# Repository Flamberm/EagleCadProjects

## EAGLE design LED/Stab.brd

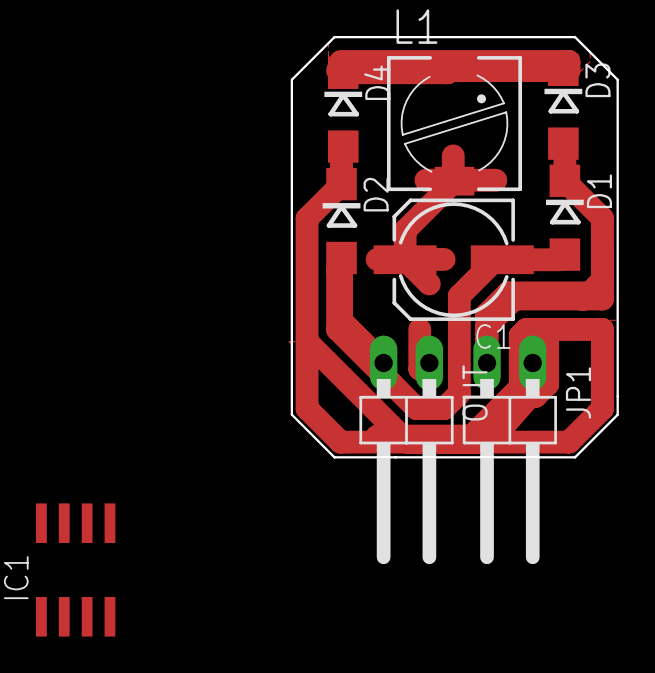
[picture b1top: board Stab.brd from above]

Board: 2 copper layers, 18.1 x 23.3 mm, 9 parts (0 on the bottom side), 5 nets.

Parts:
C1: 153CLV-0605
D1, D2, D3, D4: DO214AC
IC1: 78L12SMD; SO08
JP1: 1X02/90
L1: PIS2816
OUT: 1X02/90

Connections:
AC1: D1.C, D3.A, JP1.2
AC2: D2.C, D4.A, JP1.1
GND: C1.-, D1.A, D2.A, IC1.2, IC1.3, IC1.6, IC1.7, OUT.2
unnamed: D3.C, D4.C, L1.1
VCC: C1.+, L1.2

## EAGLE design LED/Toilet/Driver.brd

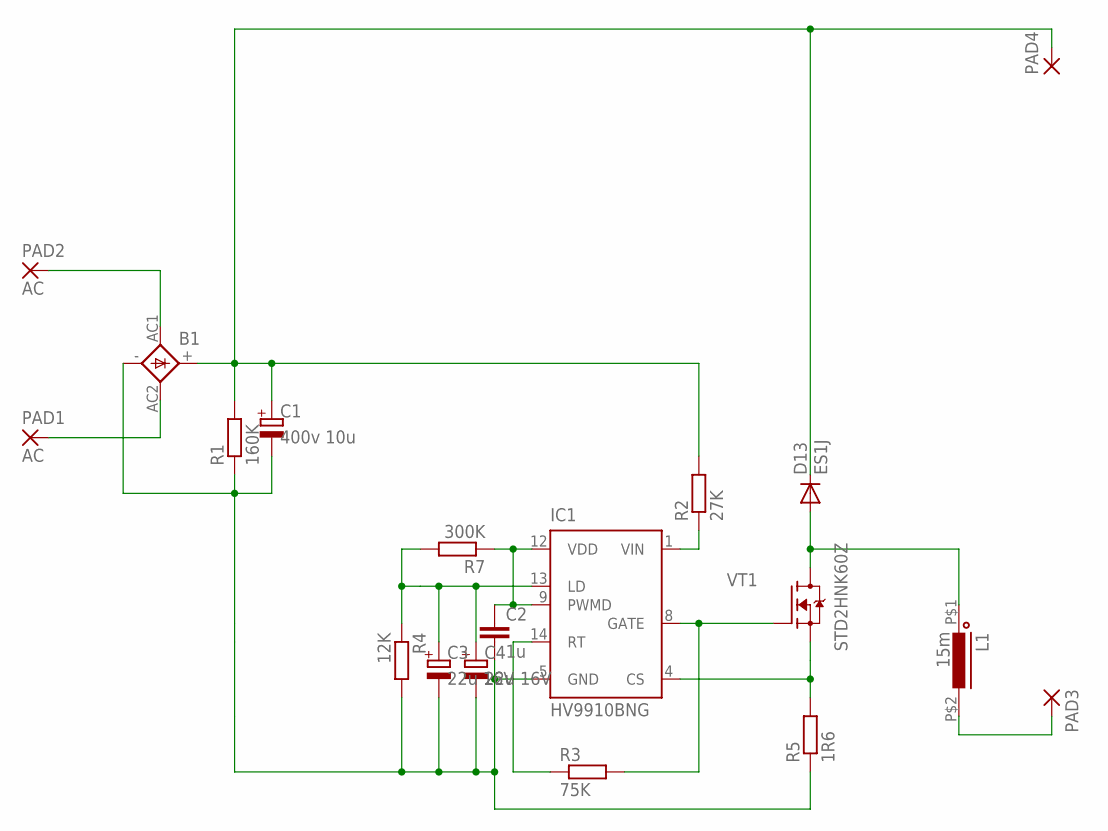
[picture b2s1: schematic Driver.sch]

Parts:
B1: BRIDGEMBS; MBS
C1: 400v 10u; E3,5-8
C2: 1u; C0805
C3, C4: 22u 16V; CT3528
D13: ES1J; DO214AC
IC1: HV9910BNG; SOIC-16NG
L1: 15m; SL1016
PAD1, PAD2: AC; SMD2,54-5,08
PAD3, PAD4: SMD5; SMD2,54-5,08
R1: 160K; MF-0125
R2: 27K; MF-2
R3: 75K; R0805
R4: 12K; R0805
R5: 1R6; MF-05
R7: 300K; R0805
VT1: STD2HNK60Z; DPAK

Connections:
unnamed: B1.AC1, PAD2.1
unnamed: B1.AC2, PAD1.1
unnamed: B1.-, C1.-, C2.2, C3.-, C4.-, IC1.5 (GND), R1.1, R4.2, R5.1
unnamed: C3.+, C4.+, IC1.13 (LD), R4.1, R7.2
unnamed: B1.+, C1.+, D13.C, PAD4.1, R1.2, R2.2
unnamed: IC1.1 (VIN), R2.1
unnamed: IC1.4 (CS), R5.2, VT1.S
unnamed: IC1.14 (RT), R3.1
unnamed: IC1.8 (GATE), R3.2, VT1.G
unnamed: L1.P$2 (2), PAD3.1
unnamed: D13.A, L1.P$1 (1), VT1.D
unnamed: C2.1, IC1.9 (PWMD), IC1.12 (VDD), R7.1

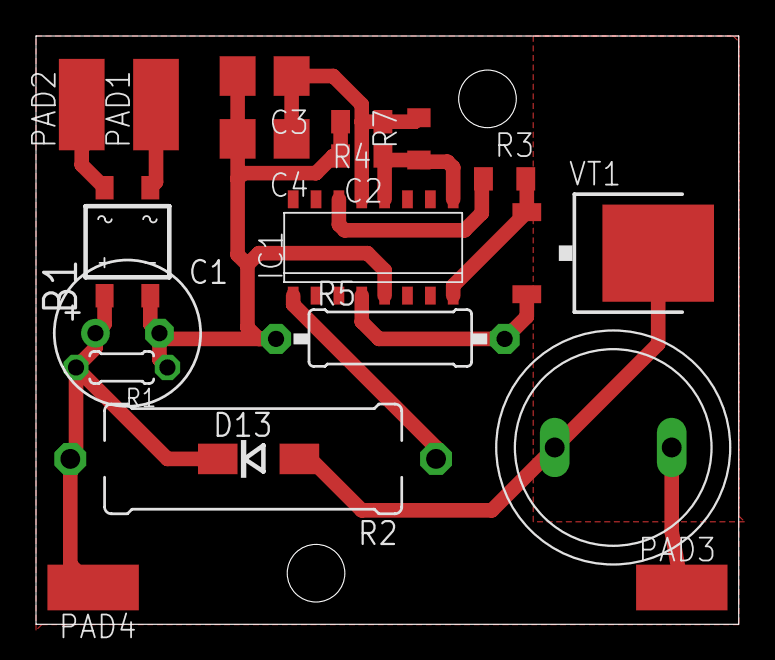
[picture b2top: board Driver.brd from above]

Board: 2 copper layers, 39.0 x 32.7 mm, 19 parts (0 on the bottom side), 12 nets.

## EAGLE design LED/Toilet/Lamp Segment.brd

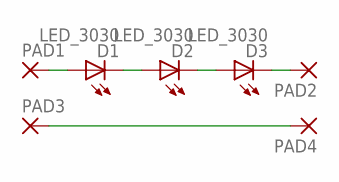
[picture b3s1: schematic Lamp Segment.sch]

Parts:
D1, D2, D3: LED_3030; LED3030
PAD1, PAD2, PAD3, PAD4: SMD5; SMD2,54-5,08

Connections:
1: D1.P$1 (A), PAD1.1
2: D1.P$2 (C), D2.P$1 (A)
3: D2.P$2 (C), D3.P$1 (A)
4: D3.P$2 (C), PAD2.1
BP: PAD3.1, PAD4.1

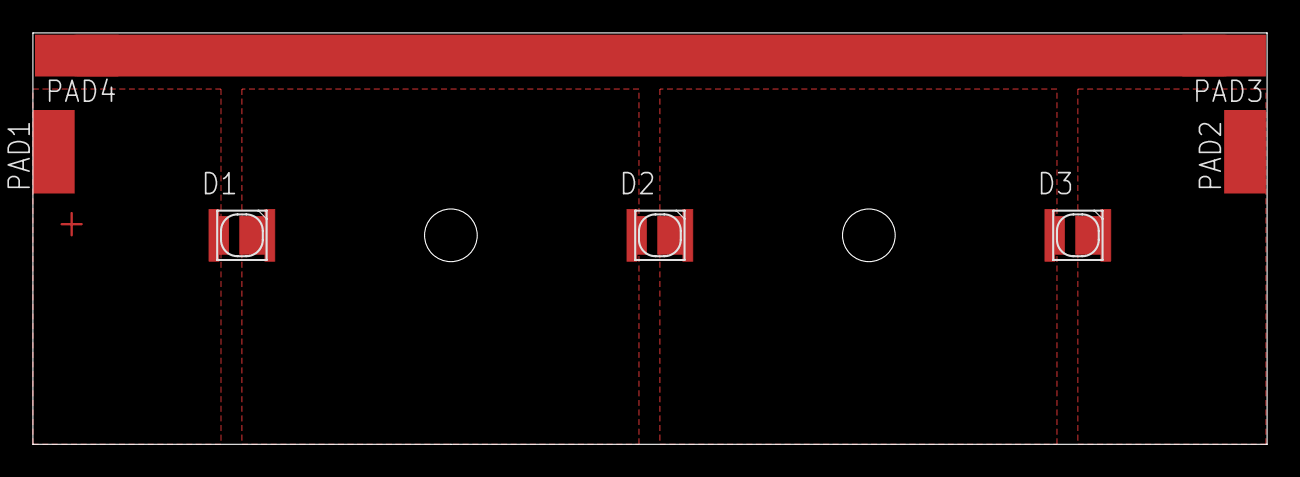
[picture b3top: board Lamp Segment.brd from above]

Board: 2 copper layers, 75.0 x 25.0 mm, 7 parts (0 on the bottom side), 5 nets.

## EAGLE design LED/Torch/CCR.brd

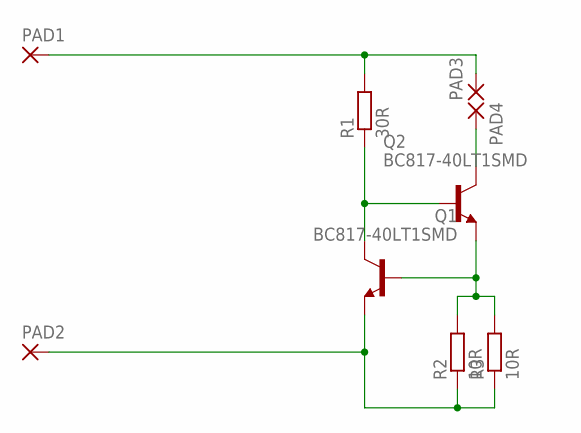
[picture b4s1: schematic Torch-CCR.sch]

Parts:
PAD1, PAD2, PAD3, PAD4: 2,15/1,0
Q1, Q2: BC817-40LT1SMD; SOT23-BEC
R1: 30R; R1206
R2, R3: 10R; R1206

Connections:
unnamed: PAD1.1, PAD3.1, R1.2
unnamed: Q1.C, Q2.B, R1.1
unnamed: PAD4.1, Q2.C
unnamed: PAD2.1, Q1.E, R2.1, R3.1
unnamed: Q1.B, Q2.E, R2.2, R3.2

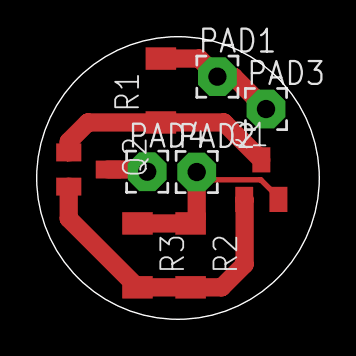
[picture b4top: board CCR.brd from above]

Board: 2 copper layers, 15.7 x 15.7 mm, 9 parts (0 on the bottom side), 5 nets.

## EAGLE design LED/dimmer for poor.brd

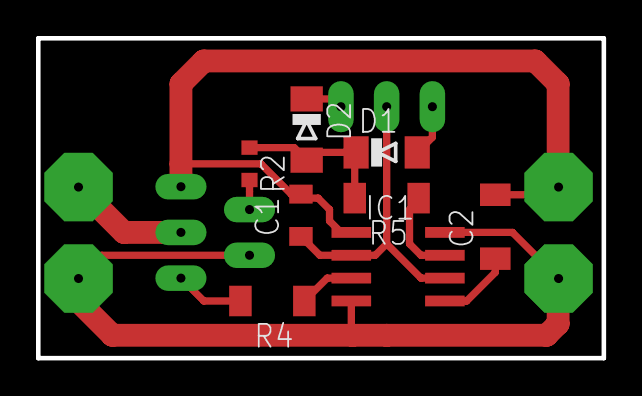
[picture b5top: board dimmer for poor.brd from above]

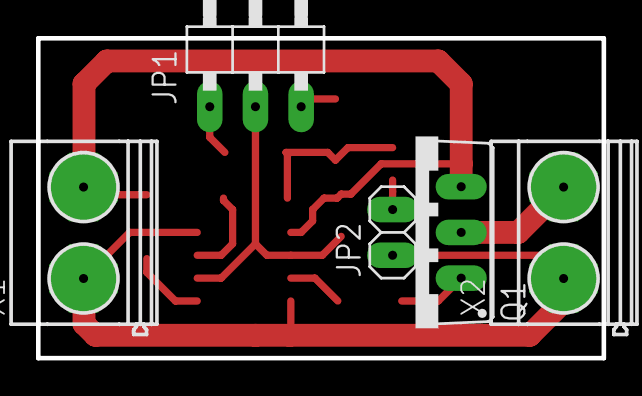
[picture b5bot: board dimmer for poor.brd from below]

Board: 2 copper layers, 31.4 x 17.8 mm, 13 parts (5 on the bottom side), 12 nets.

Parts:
C1: 560p; C0805
C2: 1000p; C1206
D1, D2: MINIMELF
IC1: LM555D; SO08
JP1: 1X03/90
JP2: 1X02
Q1: STP11NK50Z; TO220BV
R2: 1K; R0603
R4: 100R; R1206
R5: 0; R1206
X1, X2: MKDSN1,5/2-5,08

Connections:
GND: C1.2, C2.2, IC1.1, Q1.S, X1.2
unnamed: C1.1, IC1.2, IC1.6, JP1.2
unnamed: IC1.4, IC1.8, JP2.1, X1.1, X2.1
unnamed: IC1.3, R4.1
unnamed: Q1.G, R4.2
unnamed: Q1.D, X2.2
unnamed: D1.C, D2.A, R2.1, R5.2
unnamed: IC1.7, R5.1
unnamed: C2.1, IC1.5
unnamed: D1.A, JP1.1
unnamed: D2.C, JP1.3
unnamed: JP2.2, R2.2
